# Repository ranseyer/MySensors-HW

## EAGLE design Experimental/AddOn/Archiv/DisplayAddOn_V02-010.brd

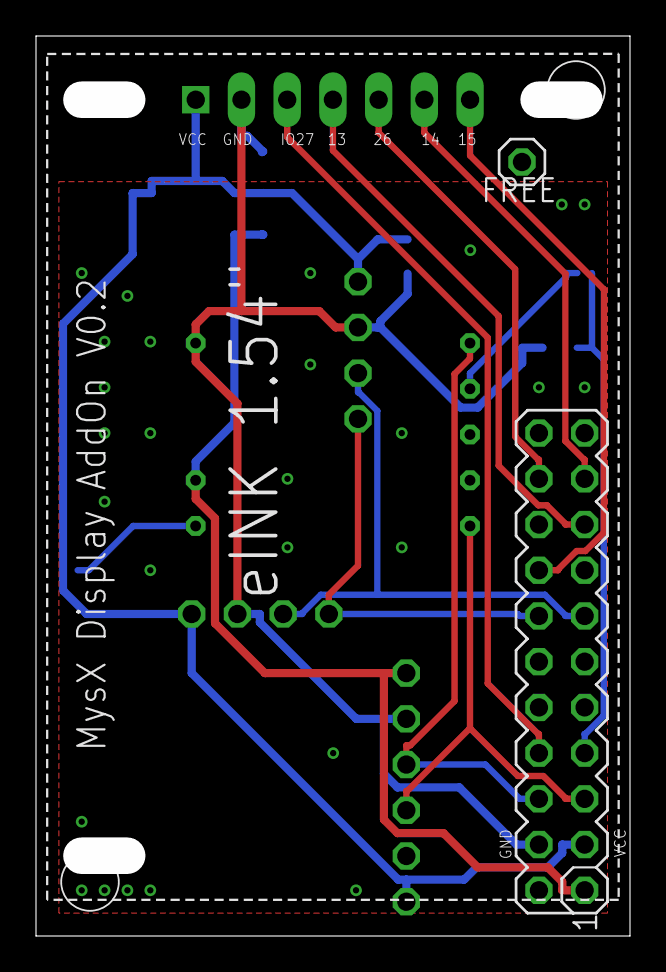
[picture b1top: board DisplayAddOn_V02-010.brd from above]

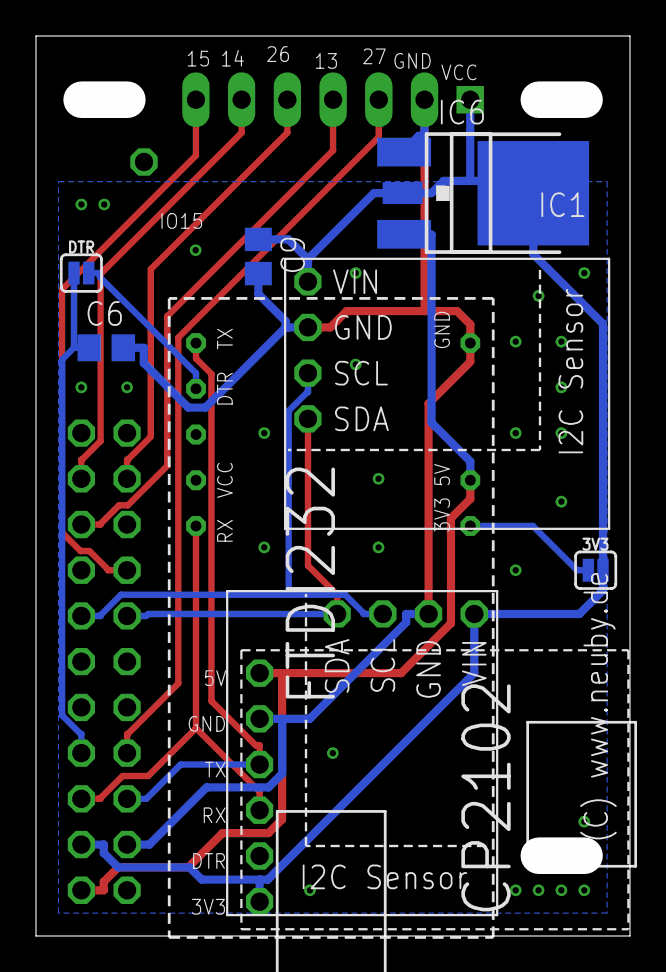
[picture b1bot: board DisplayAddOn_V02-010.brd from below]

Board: 2 copper layers, 33.0 x 50.0 mm, 13 parts (10 on the bottom side), 15 nets.

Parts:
3V3: JUMPER-SMT_2_NO_SILK; SMT-JUMPER_2_NO_SILK
C6: 2u2; C0805
C9: 22u; C0805
DTR: JUMPER-SMT_2_NO_SILK; SMT-JUMPER_2_NO_SILK
FREE: 1X01
HELTEK: ZUCZUG_1.54; ZUCZUG_1.54INCH
IC1: LD117ADT50TR; DPACK
IC6: LM1117MPX-ADJ; SOT223
MYSX: MA11-2
U$1: CP2101; CP2101-BEAKOUT
U$2, U$4: I2C-BREAKOUT; I2C_BREAKOUT
U$3: FTDI232; FTDI232-LARGE-LESS-PINS

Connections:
EN: C6.1, DTR.1, MYSX.7
GND: C6.2, C9.2, HELTEK.GND, IC1.1, IC6.1, MYSX.4, U$1.GND, U$2.GND, U$3.GND, U$4.GND
IO13: HELTEK.SDI, MYSX.17
IO14: HELTEK.CLK, MYSX.19
IO15: HELTEK.BUSY, MYSX.16
IO21: MYSX.14, U$2.SDA, U$4.SDA
IO22: MYSX.13, U$2.SCL, U$4.SCL
IO26: HELTEK.CS, MYSX.20
IO27: HELTEK.D/C, MYSX.8
unnamed: DTR.2, U$3.DTR
unnamed: 3V3.1, U$3.3V3
RXD0: MYSX.6, U$1.TXD, U$3.TXD
TXD0: MYSX.5, U$1.RXD, U$3.RXD
UREG: IC1.3, IC6.3, MYSX.1, U$1.5V, U$3.5V
VCC: 3V3.2, C9.1, HELTEK.VCC, IC1.4, IC6.2, IC6.TAB, MYSX.3, U$1.3V3, U$2.VIN, U$4.VIN

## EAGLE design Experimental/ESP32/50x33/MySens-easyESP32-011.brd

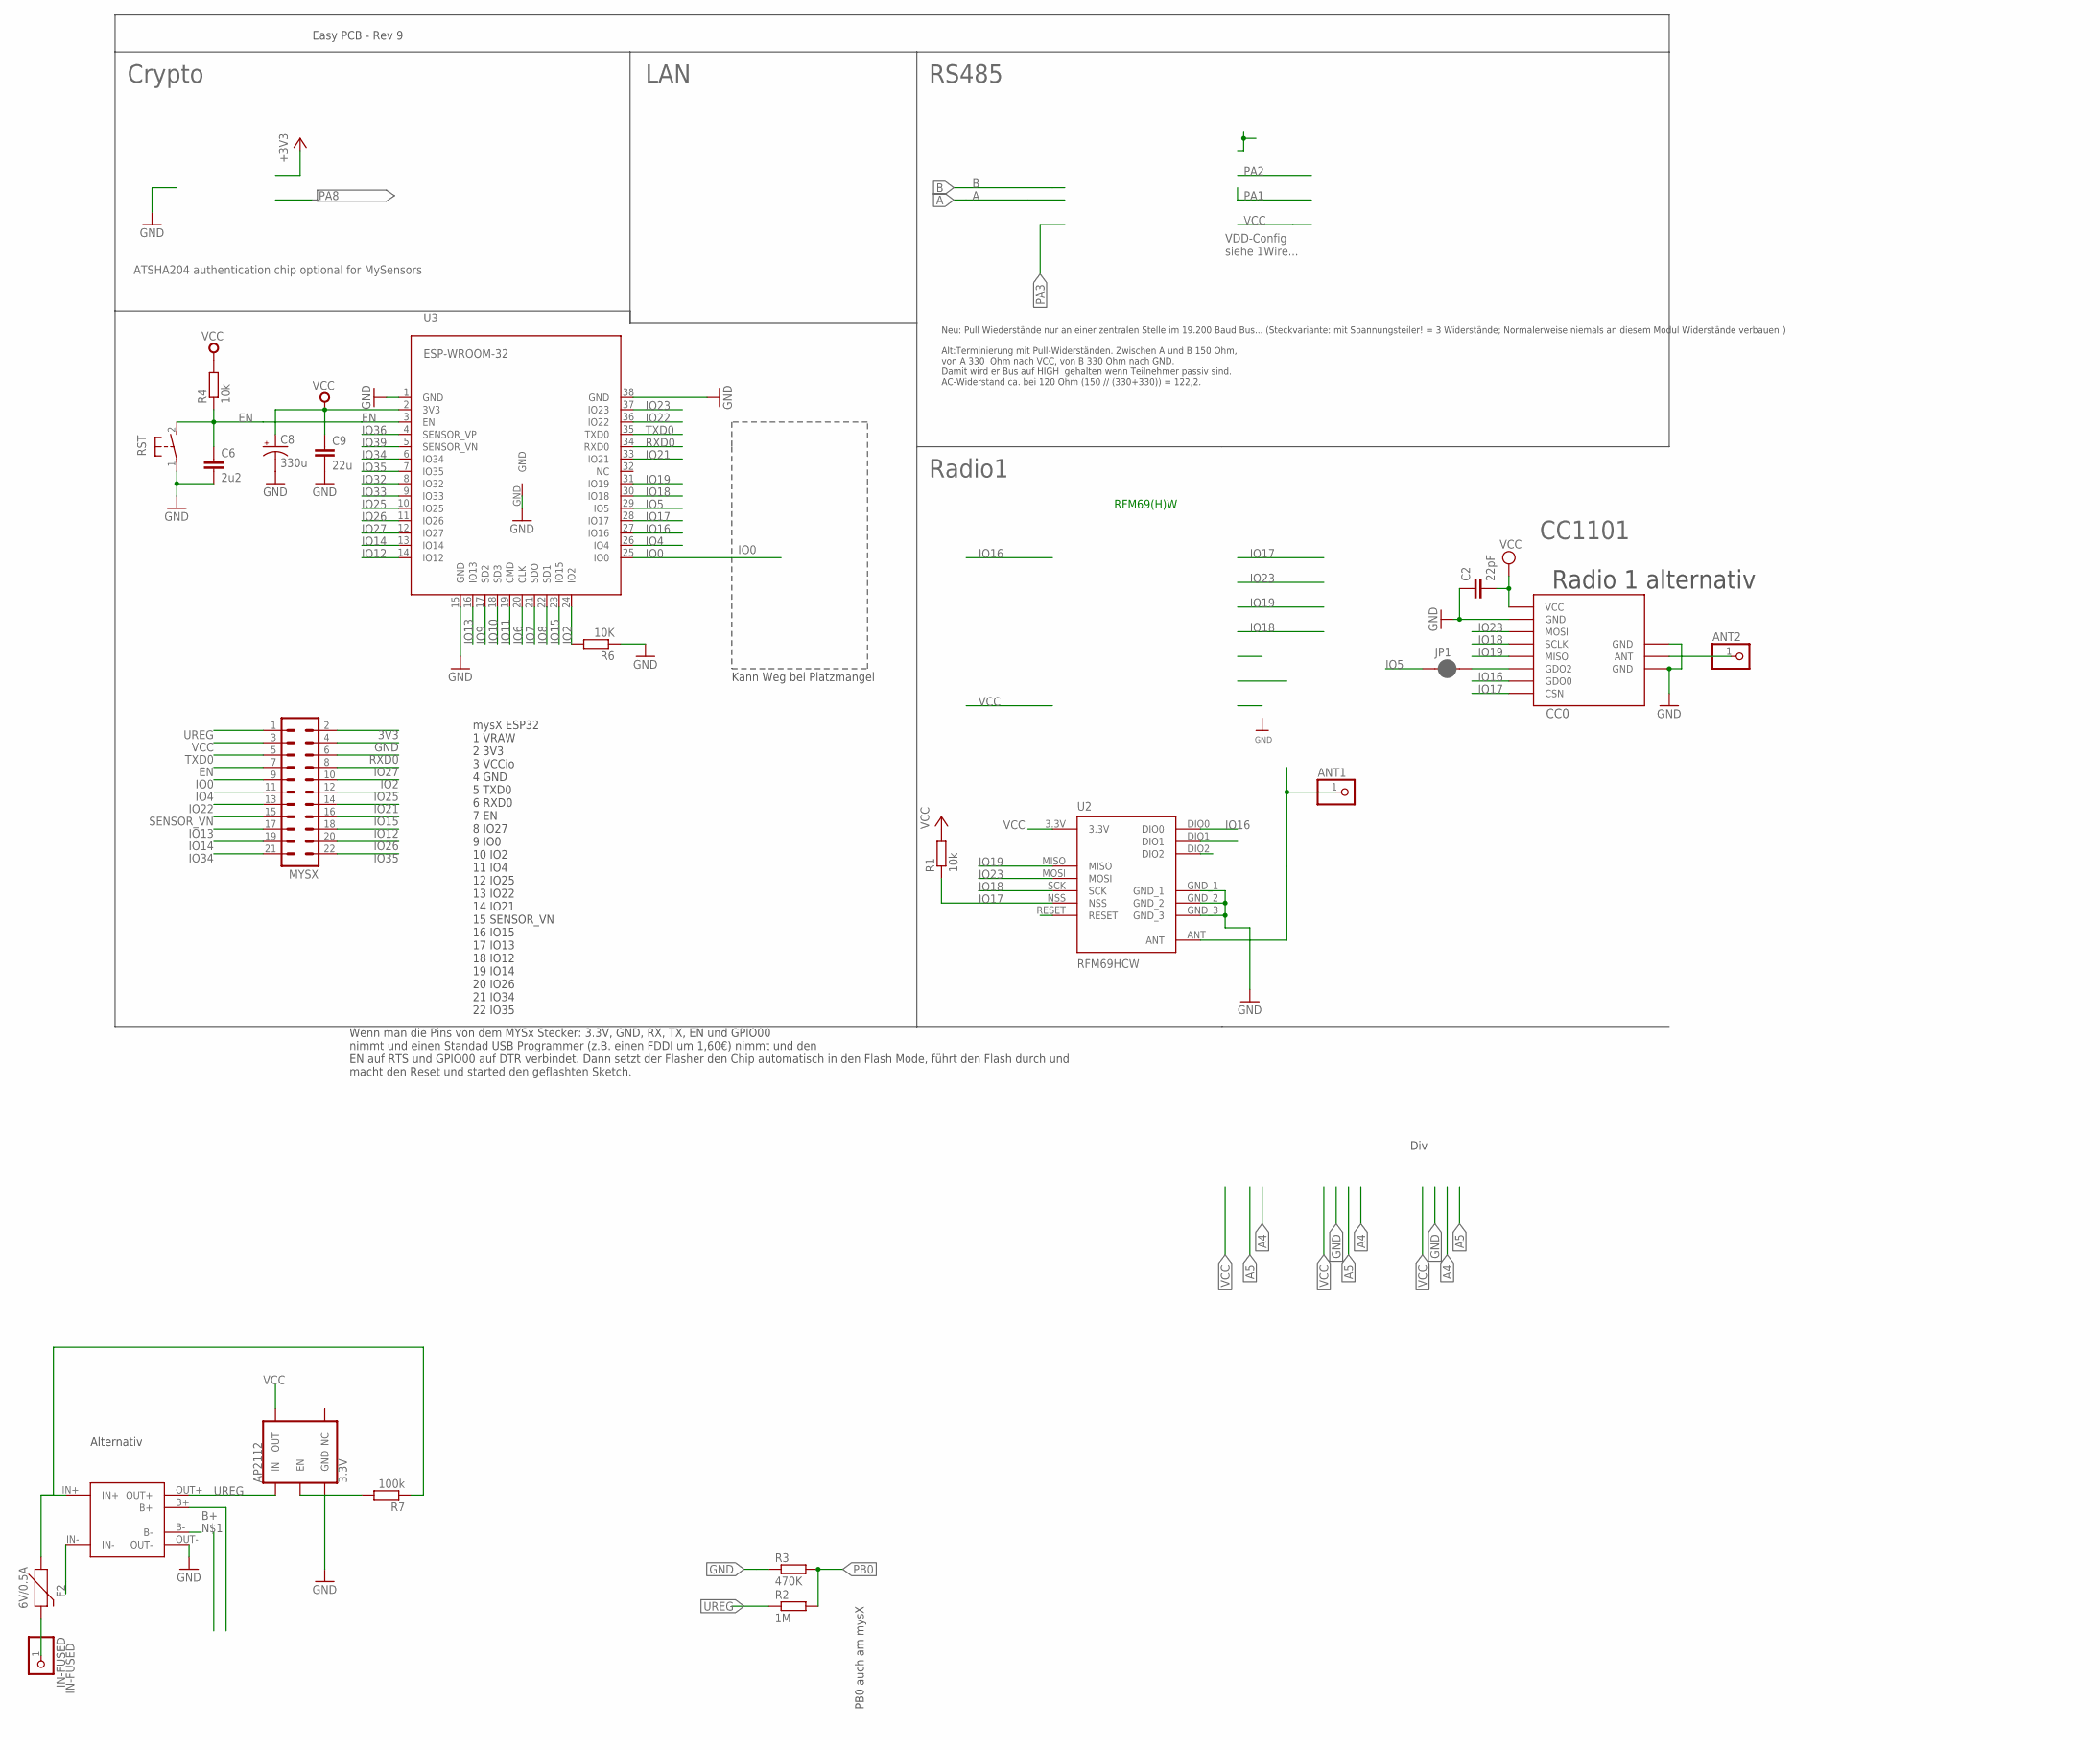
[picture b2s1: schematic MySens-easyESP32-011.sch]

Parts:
ANT1, ANT2: PINHD-1X1; 1X01
AP2112: 3.3V; SOT23-5
C2: 22pF; C0805
C6: 2u2; C0805
C8: 330u; VISHAY_C
C9: 22u; C0805
CC0: CC1101; CC1101_MODULE1_SMD
F2: 6V/0.5A; 1206
IN-FUSED: PINHD-1X1; 1X01
JP1: JUMPER-SMT_2_NC_PASTE_NO-SILK; SMT-JUMPER_2_NC_PASTE_NO-SILK
MYSX: MA11-2
R1, R4: 10k; M0805
R2: 1M; M0805
R3: 470K; M0805
R6: 10K; M0805
R7: 100k; M0805
RST: DTSM-3
TP4056: TP4056-MODULE; TP4056-LITHIUM-PROTECTED-MODULE
U2: RFM69HCW; RFM69HCW-XXXS2
U3: ESP-WROOM-32

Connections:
3V3: MYSX.2
ANT0: ANT2.1, CC0.ANT
ANT1: ANT1.1, U2.ANT
B+: TP4056.B+
EN: C6.1, MYSX.7, R4.1, RST.2, U3.3 (EN)
GND: AP2112.2 (GND), C2.1, C6.2, C8.-, C9.2, CC0.GND@0 (GND), CC0.GND@1 (GND), CC0.GND@2 (GND), MYSX.4, R3.1, R6.1, RST.1, TP4056.OUT-, U2.GND_1, U2.GND_2, U2.GND_3, U3.1 (GND), U3.15 (GND), U3.38 (GND), U3.GND
IN++: F2.1, R7.1, TP4056.IN+
IN-: TP4056.IN-
IN-FUSED: F2.2, IN-FUSED.1
IO0: MYSX.9, U3.25 (IO0)
IO2: MYSX.10, R6.2, U3.24 (IO2)
IO4: MYSX.11, U3.26 (IO4)
IO5: JP1.1, U3.29 (IO5)
IO6: U3.20 (CLK)
IO7: U3.21 (SDO)
IO8: U3.22 (SD1)
IO9: U3.17 (SD2)
IO10: U3.18 (SD3)
IO11: U3.19 (CMD)
IO12: MYSX.18, U3.14 (IO12)
IO13: MYSX.17, U3.16 (IO13)
IO14: MYSX.19, U3.13 (IO14)
IO15: MYSX.16, U3.23 (IO15)
IO16: CC0.GDO0, U2.DIO0, U3.27 (IO16)
IO17: CC0.CSN, R1.1, U2.NSS, U3.28 (IO17)
IO18: CC0.SCLK, U2.SCK, U3.30 (IO18)
IO19: CC0.MISO, U2.MISO, U3.31 (IO19)
IO21: MYSX.14, U3.33 (IO21)
IO22: MYSX.13, U3.36 (IO22)
IO23: CC0.MOSI, U2.MOSI, U3.37 (IO23)
IO25: MYSX.12, U3.10 (IO25)
IO26: MYSX.20, U3.11 (IO26)
IO27: MYSX.8, U3.12 (IO27)
IO32: U3.8 (IO32)
IO33: U3.9 (IO33)
IO34: MYSX.21, U3.6 (IO34)
IO35: MYSX.22, U3.7 (IO35)
IO36: U3.4 (SENSOR_VP)
IO39: U3.5 (SENSOR_VN)
MAYBE_IO5: CC0.GDO2, JP1.2
unnamed: AP2112.3 (EN), R7.2
PB0: R2.2, R3.2
RXD0: MYSX.6, U3.34 (RXD0)
SENSOR_VN: MYSX.15
TXD0: MYSX.5, U3.35 (TXD0)
UREG: AP2112.1 (IN), MYSX.1, R2.1, TP4056.OUT+
VCC: AP2112.5 (OUT), C2.2, C8.+, C9.1, CC0.VCC, MYSX.3, R1.2, R4.2, U2.3.3V, U3.2 (3V3)

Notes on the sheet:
Easy PCB - Rev 9
ATSHA204 authentication chip optional for MySensors
VDD-Config siehe 1Wire...
Neu: Pull Wiederstände nur an einer zentralen Stelle im 19.200 Baud Bus... (Steckvariante: mit Spannungsteiler! = 3 Widerstände; Normalerweise niemals an diesem Modul Widerstände verbauen!) Alt:Terminierung mit Pull-Widerständen. Zwischen A und B 150 Ohm, von A 330 Ohm nach VCC, von B 330 Ohm nach 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
RFM69(H)W
Div
mysX ESP32 1 VRAW 2 3V3 3 VCCio 4 GND 5 TXD0 6 RXD0 7 EN 8 IO27 9 IO0 10 IO2 11 IO4 12 IO25 13 IO22 14 IO21 15 SENSOR_VN 16 IO15 17 IO13 18 IO12 19 IO14 20 IO26 21 IO34 22 IO35
PB0 auch am mysX
Radio1
LAN
RS485
Crypto
Radio 1 alternativ
CC1101
Kann Weg bei Platzmangel
Wenn man die Pins von dem MYSx Stecker: 3.3V, GND, RX, TX, EN und GPIO00 nimmt und einen Standad USB Programmer (z.B. einen FDDI um 1,60€) nimmt und den EN auf RTS und GPIO00 auf DTR verbindet. Dann setzt der Flasher den Chip automatisch in den Flash Mode, führt den Flash durch und macht den Reset 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
Alternativ

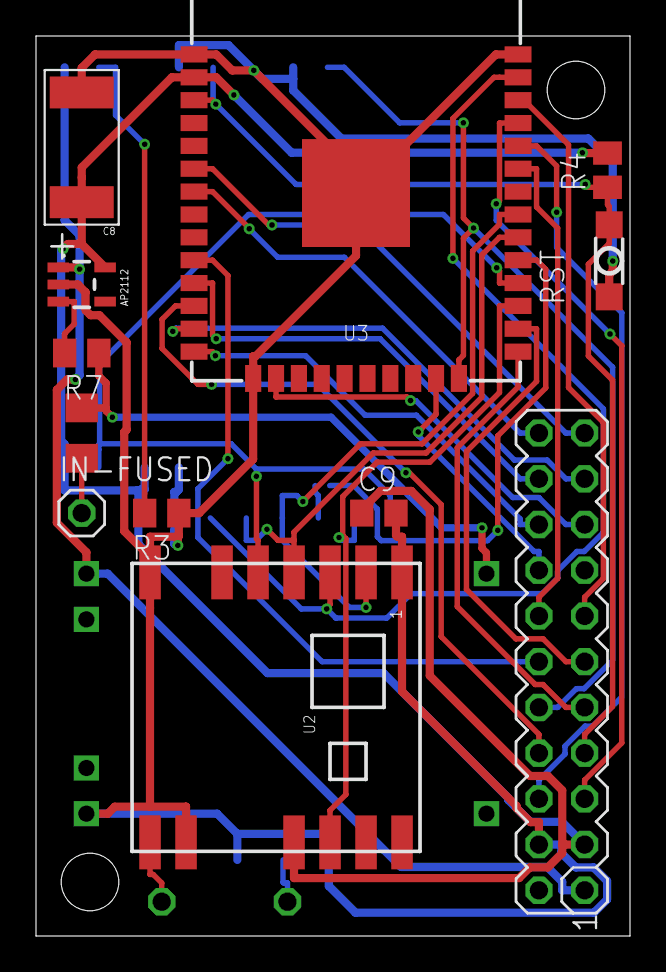
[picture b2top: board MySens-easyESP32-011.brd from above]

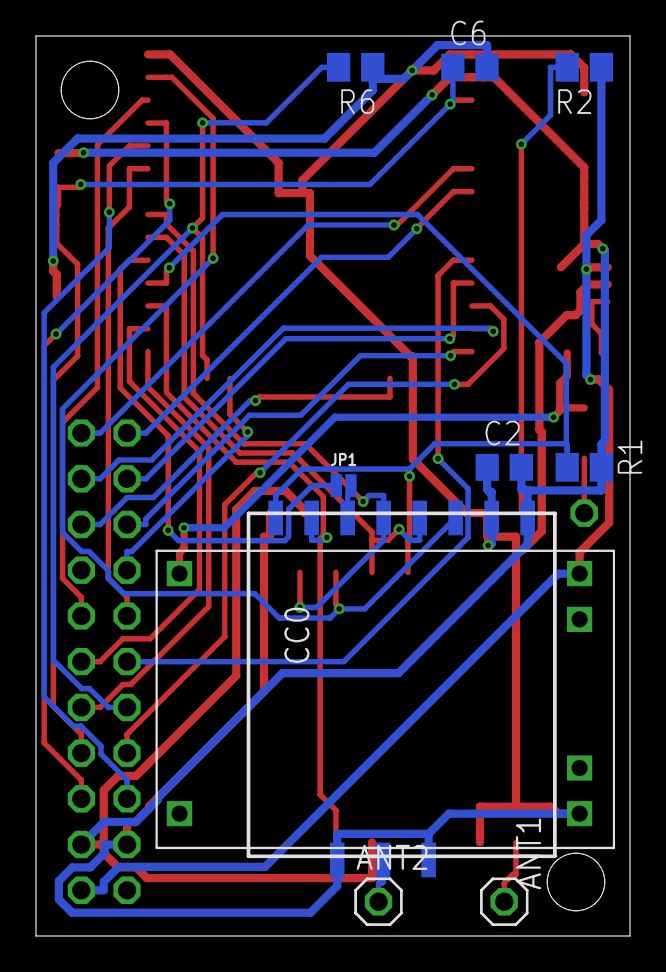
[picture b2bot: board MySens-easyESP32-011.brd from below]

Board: 2 copper layers, 33.0 x 50.0 mm, 22 parts (10 on the bottom side), 33 nets.

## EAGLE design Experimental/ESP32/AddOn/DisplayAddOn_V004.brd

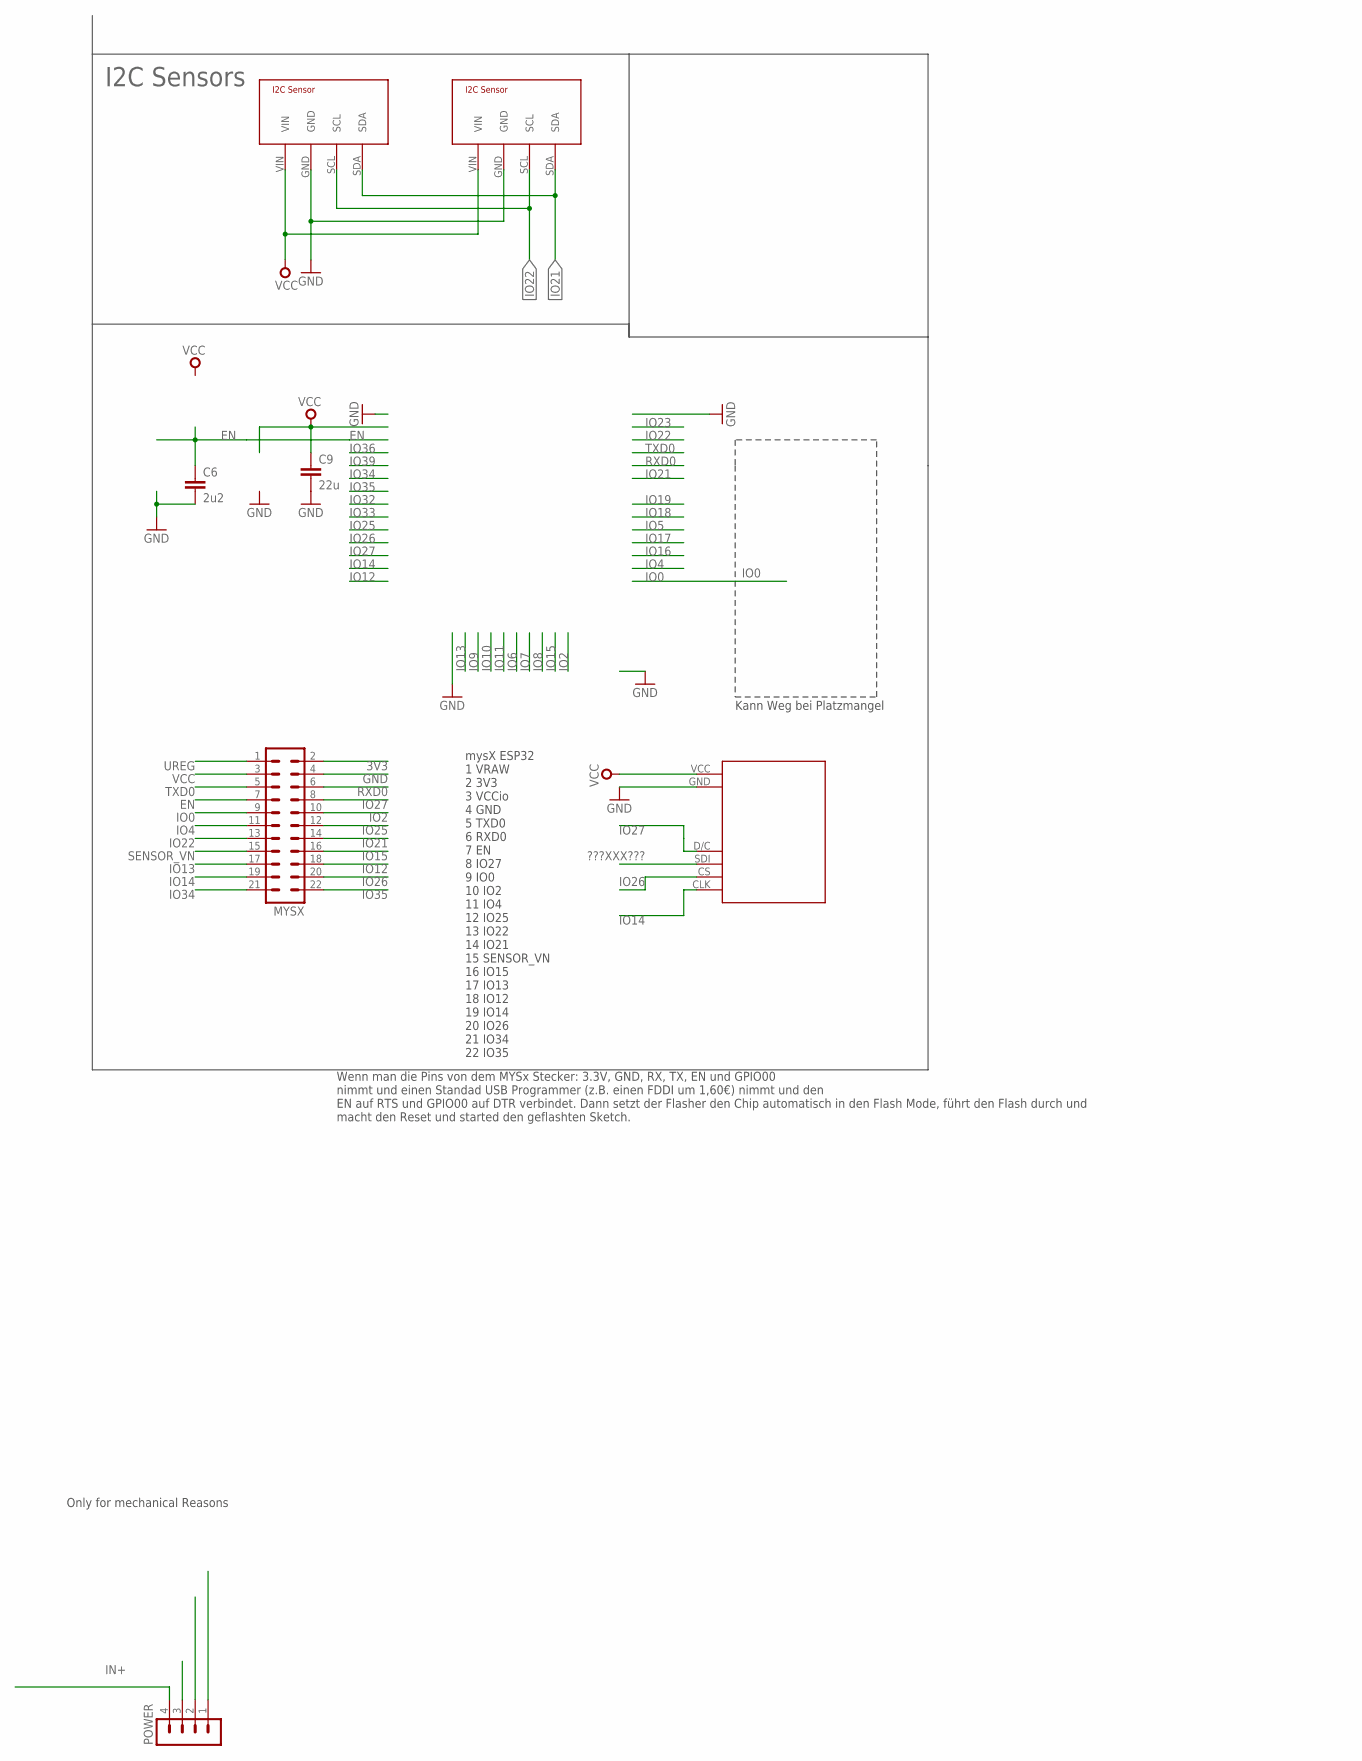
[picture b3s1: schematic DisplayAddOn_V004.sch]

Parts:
C6: 2u2; C0805
C9: 22u; C0805
MYSX: MA11-2
POWER: MA04-1
U$1: HELTEC_1.54STANDARD1; HELTEC_1.54INCH
U$2, U$4: I2C-BREAKOUT; I2C_BREAKOUT

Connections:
3V3: MYSX.2
???XXX???: U$1.SDI
B+: POWER.1
B-: POWER.2
EN: C6.1, MYSX.7
GND: C6.2, C9.2, MYSX.4, U$1.GND, U$2.GND, U$4.GND
IN+: POWER.4
IO0: MYSX.9
IO2: MYSX.10
IO4: MYSX.11
IO12: MYSX.18
IO13: MYSX.17
IO14: MYSX.19, U$1.CLK
IO15: MYSX.16
IO21: MYSX.14, U$2.SDA, U$4.SDA
IO22: MYSX.13, U$2.SCL, U$4.SCL
IO25: MYSX.12
IO26: MYSX.20, U$1.CS
IO27: MYSX.8, U$1.D/C
IO34: MYSX.21
IO35: MYSX.22
RXD0: MYSX.6
SENSOR_VN: MYSX.15
TXD0: MYSX.5
UREG: MYSX.1
VCC: C9.1, MYSX.3, U$1.VCC, U$2.VIN, U$4.VIN

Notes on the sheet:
mysX ESP32 1 VRAW 2 3V3 3 VCCio 4 GND 5 TXD0 6 RXD0 7 EN 8 IO27 9 IO0 10 IO2 11 IO4 12 IO25 13 IO22 14 IO21 15 SENSOR_VN 16 IO15 17 IO13 18 IO12 19 IO14 20 IO26 21 IO34 22 IO35
I2C Sensors
Kann Weg bei Platzmangel
Wenn man die Pins von dem MYSx Stecker: 3.3V, GND, RX, TX, EN und GPIO00 nimmt und einen Standad USB Programmer (z.B. einen FDDI um 1,60€) nimmt und den EN auf RTS und GPIO00 auf DTR verbindet. Dann setzt der Flasher den Chip automatisch in den Flash Mode, führt den Flash durch und macht den Reset 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
Only for mechanical Reasons

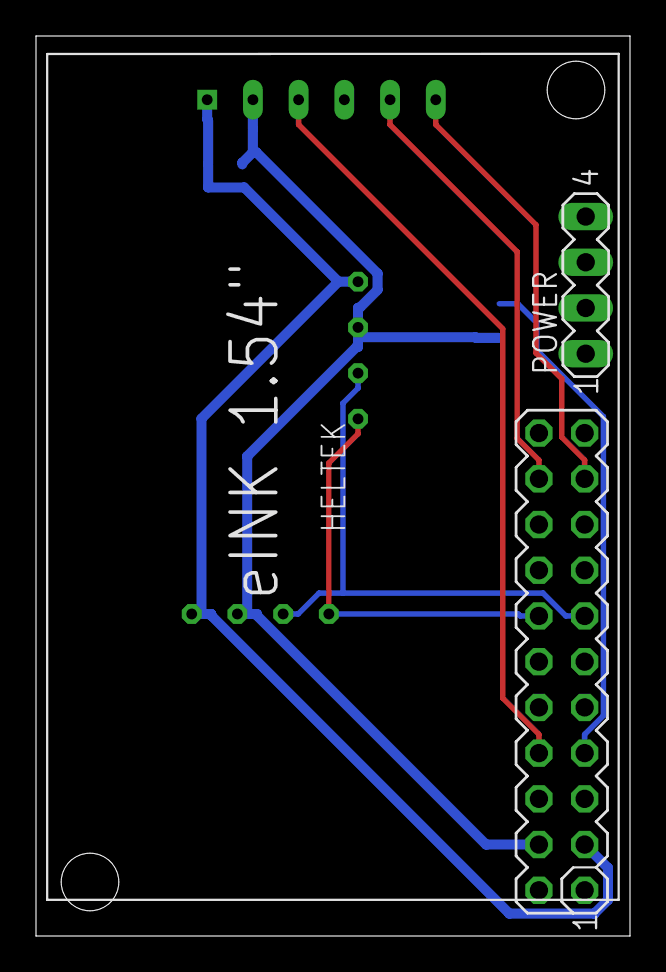
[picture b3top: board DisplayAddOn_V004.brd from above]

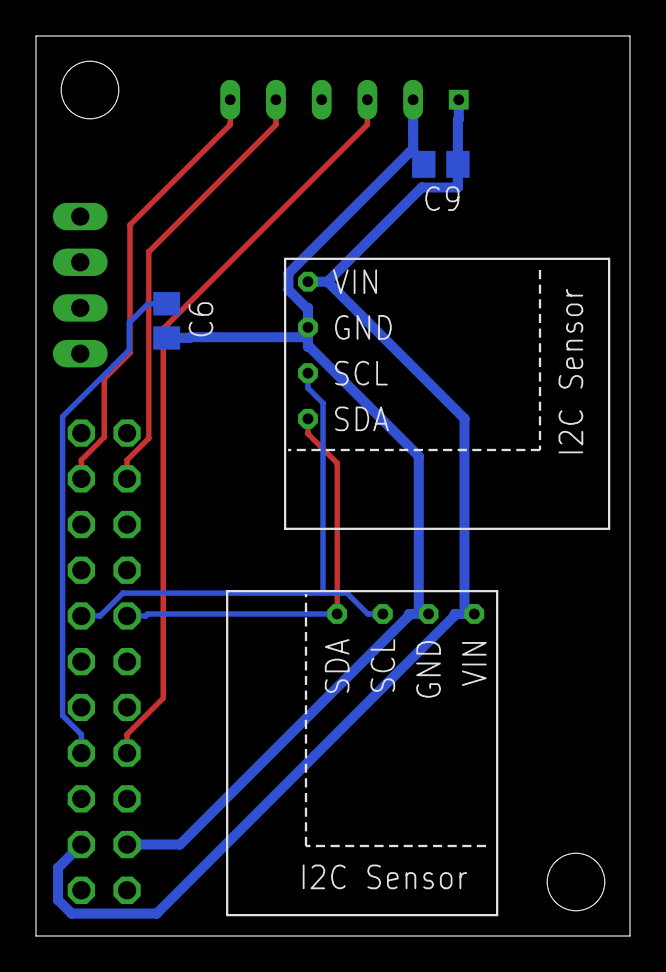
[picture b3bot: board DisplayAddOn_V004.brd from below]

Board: 2 copper layers, 33.0 x 50.0 mm, 7 parts (4 on the bottom side), 8 nets.

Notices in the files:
parts and their libraries:
SparkFun-Jumpers: Licensing: Creative Commons ShareAlike 4.0 International - https://creativecommons.org/licenses/by-sa/4.0
microbuilder: This work is placed in the public domain, and may be freely used for commercial and non-commercial work with the following conditions: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
